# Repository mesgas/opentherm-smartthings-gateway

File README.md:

# OpenTherm ⇄ SmartThings gateway

A DIY **OpenTherm** gateway based on the ESP32-C3. It sits between your room thermostat and your boiler,
relays everything transparently, and lets you read and control the boiler from **SmartThings** through a
native **Edge driver** (no Matter, no Home Assistant).

```
thermostat ── T1/T2 [Slave shield]  ESP32-C3  [Master shield] B1/B2 ── boiler
                                       │ Wi-Fi, HTTP/JSON
                        SmartThings hub (Edge driver)  ──  SmartThings app
```

**Background:** I (the author) switched to Home Assistant two years ago and I am very happy with it. This project
was built for my father's boiler, in a household that still runs SmartThings. It is shared in the hope that it is
useful to other SmartThings users with an OpenTherm boiler. The HTTP/JSON API below can also be used from any
other home automation system.

---

## ⚠️ Important warnings

- **Experimental project, provided "as is", with no warranty of any kind** (see [LICENSE](LICENSE)).
- It involves **a gas appliance**. The gateway is wired **in series** between thermostat and boiler: if the
  ESP loses power or hangs, the thermostat can no longer talk to the boiler. Decide for yourself what
  happens in your installation in that case.
- The gateway can **switch heating off**, **cap the flow temperature**, and in "App command" mode it
  **replaces the thermostat**. It is not a safety device.
- Wiring on the boiler terminals must be done **with the power off** and, if you are not experienced,
  **by a qualified technician**. Never work on gas or 230 V parts.
- This project is not a product of any boiler manufacturer, DIYLess, Samsung or SmartThings.

---

## What it does

- **Relays transparently** every OpenTherm message between thermostat and boiler (it keeps working
  when Wi-Fi or SmartThings are unavailable).
- **Reads all the data that passes through** and asks the boiler for more in the thermostat's pauses:
  flow, return and hot water temperature, modulation, flame, faults, etc. (depending on what your boiler
  supports).
- **Controls from SmartThings:**
  - heating on/off (clears the "CH enable" bit in the status message);
  - domestic hot water on/off and setpoint;
  - flow temperature cap;
  - **App command**: the gateway regulates the room temperature towards a target set from SmartThings,
    using the temperature measured by the original thermostat;
  - **Auto flow**: the thermostat decides when to heat, the gateway computes the lowest possible flow
    temperature (useful with condensing boilers);
  - optional NTC outdoor probe: outdoor temperature, also provided to the thermostat.
- A local **HTTP/JSON API** for diagnostics and integration.

## Hardware

| Part | Notes |
|---|---|
| LOLIN (WEMOS) **C3 mini** | ESP32-C3, D1 mini form factor |
| **DIYLess Master OpenTherm shield** | boiler side (B1/B2) |
| **DIYLess Slave OpenTherm shield** | thermostat side (T1/T2) |
| Expansion shield (optional) | to mount the three boards side by side |
| 10 kΩ NTC probe (optional) | for the outdoor temperature, with a 10 kΩ resistor and a 100 nF capacitor |

Pins used (D1 mini position → C3 mini GPIO):

| Function | Position | GPIO |
|---|---|---|
| Master, OT input | D2 | 8 |
| Master, OT output | D1 | 10 |
| Slave, OT input | D6 | 0 |
| Slave, OT output | D7 | 4 |
| Outdoor probe (optional) | A0 | 3 |

They can be changed in [`src/config.h`](src/config.h). GPIO8 is a strapping pin of the ESP32-C3: if flashing
fails with the master shield mounted, remove the shield or hold BOOT.

**Outdoor probe (optional):** `3V3 ── R 10 kΩ ──┬── NTC ── GND`, with 100 nF between the node and GND and
the node connected to GPIO3. Enable it only after wiring it: `POST /api/settings {"outdoorEnabled":true}`.

## Firmware

1. Copy `src/secrets.example.h` to `src/secrets.h` and fill in your Wi-Fi (2.4 GHz). This file must never be
   committed (it is already in `.gitignore`).
2. `pio run -t upload` over USB the first time; later `pio run -e ota -t upload` for over-the-air updates
   (set `upload_port` in `platformio.ini`).
3. The serial monitor (115200) shows the IP, the relayed messages and the IDs requested by the thermostat.
4. Give the ESP a **fixed IP** in your router.
5. Optional: the ESP is reachable as `http://otgw.local/`. To change the name, add `#define HOSTNAME "my-boiler"` to `src/secrets.h`
   (and use it as `upload_port` in `platformio.ini`). Some phones cannot resolve `.local` names: use the IP address, or add a
   static DNS entry in your router.

Every boiler supports different OpenTherm IDs: use `GET /api/probe?id=N` to test yours and adapt
`POLL_IDS` in `config.h`.

## SmartThings driver (Edge)

**Quick install (driver only):** open this invitation link with the account that owns your hub, enroll the hub and
install the driver "OpenTherm Gateway" from the channel:

<https://bestow-regional.api.smartthings.com/invite/a5z2RPnwDj1n>

The custom capabilities live in the author's SmartThings namespace and should be usable from any account,
but this has only been tested on the author's account. Feedback is welcome (open an issue).

To build and publish your own copy (recommended if you want to modify anything), follow the steps below.

You need the [SmartThings CLI](https://github.com/SmartThingsCommunity/smartthings-cli) (on the first command
a browser opens for sign-in) and a hub that supports Edge drivers.

1. **Custom capabilities** (`capabilities/` folder): modulation, maximum flow temperature, hot water setpoint,
   boiler status. For each one:
   ```
   smartthings capabilities:create -i capabilities/<name>.json
   smartthings capabilities:presentation:create <namespace>.<name> --capability-version 1 -i capabilities/presentations/<name>.json
   smartthings capabilities:translations:upsert <namespace>.<name> --capability-version 1 -i capabilities/translations/<name>.it.json
   ```
2. In `driver/profiles/opentherm-gateway.yml` and in `driver/src/init.lua` replace the namespace
   `bookmusic32648` with **your own** namespace (the one assigned by your first `capabilities:create`).
3. Create a private channel, publish the driver and install it on your hub:
   ```
   smartthings edge:channels:create          (type DRIVER)
   smartthings edge:channels:enroll <hub-id> --channel <channel-id>
   smartthings edge:drivers:package driver --channel <channel-id> --hub <hub-id>
   ```
4. In the SmartThings app: add device → scan nearby → "OpenTherm Gateway", then in the device settings enter
   the **IP address of the ESP**.

If you change the **structure** of the profile (components or capabilities moved), delete the device in the
app and add it again; otherwise the app may show connection errors.

> **Note on languages:** the user-facing labels of the SmartThings device (component names in the profile
> and the capability presentations) are in Italian, because that is the language of the original household.
> Everything else (code, comments, logs, API, documentation) is in English. To localize the UI, edit the
> `label` fields in `driver/profiles/opentherm-gateway.yml` and the labels in `capabilities/presentations/`
> and `capabilities/translations/`.

### Device in SmartThings

Component ids in the profile are Italian technical identifiers (`main` = house, `comandoapp` = app command,
`riscaldamento` = heating, `mandataauto` = auto flow, `sanitaria` = hot water, `caldaia` = boiler,
`ritorno` = return, `esterna` = outdoor).

| Component | Content |
|---|---|
| Casa (House) | room temperature (from the original thermostat), Off/Heat mode, target, state |
| Comando da app (App command) | on = the app regulates, off = the wall thermostat decides |
| Riscaldamento (Heating) | switch, maximum flow temperature |
| Mandata auto (Auto flow) | switch |
| Acqua calda (Hot water) | switch, setpoint, temperature |
| Caldaia (Boiler) | flow temperature, modulation, status (flame, heating, hot water, thermostat, fault) |
| Ritorno, Esterna (Return, Outdoor) | temperature |

## Statistics page

Open `http://otgw.local/` (or the IP of the ESP) in a browser on your local network. Two views, switched with the
buttons at the top:

- **24 h:** one point every 5 minutes (stored per minute).
- **30 d:** one point every 3 hours (stored every 30 minutes).

Both show: flame-on time, heating and hot water time, burner starts, average modulation while the flame is on, the
share of burner time spent condensing (return below ~55 °C), and charts of temperatures (house, outdoor, flow,
return, requested flow), modulation/flame and heating/hot water duty. The page is Italian or English depending on
the browser language.

**Memory and persistence:** the last 24 hours are kept in RAM (about 26 KB, one bucket per minute) and are **cleared
when the ESP restarts**. The last 30 days (about 35 KB, one bucket per 30 minutes) are also kept in RAM but are
saved to flash (LittleFS) every hour and right before an OTA update, so they survive restarts, losing at most the
last hour. Lifetime burner hours and starts are saved to NVS every 30 minutes. Heavy requests (`/api/stats`,
`/api/history`) are limited to one every 2 seconds, because on a single core a flood of Wi-Fi traffic can disturb
the OpenTherm timing. The statistics are estimates built from the data the boiler reports.

## API

- `GET /api/state` — full state as JSON (`null` = value not available)
- `POST /api/settings` — JSON with one or more of: `chEnable`, `dhwEnable`, `chMax`, `dhwSetpoint`,
  `roomControl`, `roomTarget`, `flowAuto`, `outdoorEnabled`
- `GET /api/ids` — OpenTherm IDs requested by the thermostat and rejected by the boiler
- `GET /api/probe?id=N` — test read of one ID (read-only)
- `GET /` — statistics page
- `GET /api/stats[?range=30d]` — summary of the last 24 hours (default) or 30 days
- `GET /api/history[?range=30d][&step=N]` — history in points of N minutes (24 h, N ≥ 5) or N half-hours (30 d, N from 1 to 48)

If `API_TOKEN` in `secrets.h` is not empty, POST requests need the `X-Token` header. There is no encryption:
use it only on a trusted local network.

## Regulation (to be tuned)

The room temperature regulator (hysteresis + PI) and "Auto flow" use the `CTRL_*` parameters in
[`src/config.h`](src/config.h). The starting values are conservative but **theoretical**: they must be tuned by
watching how your house behaves. If your boiler does not provide the outdoor temperature, the flow ceiling is
fixed; with the outdoor probe it follows a heating curve.

## Known limitations

- The gateway has only been tested on a single installation.
- The API is not encrypted.
- With the gateway in series, an ESP failure interrupts the thermostat–boiler dialogue.
- The custom capabilities belong to a namespace: use your own if you want to modify them.

## Credits and license

- [OpenTherm Library](https://github.com/ihormelnyk/opentherm_library) by Ihor Melnyk (MIT).
- OpenTherm shields by [DIYLess](https://diyless.com).
- [ArduinoJson](https://arduinojson.org) by Benoit Blanchon (MIT).
- License of this project: **MIT** (see [LICENSE](LICENSE)).

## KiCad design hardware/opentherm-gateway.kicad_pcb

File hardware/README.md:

# Gateway PCB

A single compact board for the OpenTherm gateway: it replaces the LOLIN C3 mini + the two DIYLess
master/slave shields. It sits between the boiler and the original thermostat and runs the same
firmware as the breadboard version (`src/`, environment `gateway_pcb`).

> **Status: designed, DRC/ERC clean, not yet fabricated.** The OpenTherm front end is taken from an
> existing, working open design (see *Origin*), but the changes listed below are untested until the
> first board is built. Follow the bring-up sequence before connecting the boiler.

| | |
|---|---|
| Size | 56 x 42 mm, 4 layers (F / GND / GND+routing / B), parts on both sides |
| MCU | ESP32-C3-WROOM-02-N4 (Wi-Fi 2.4 GHz, antenna toward the top edge, nothing under it) |
| Power | USB-C (also native USB for flashing) **or** 5 V screw terminal J5; the two are OR-ed with Schottky diodes |
| Bus | J1 `BOILER` and J2 `THERM` (OpenTherm, polarity-free), 28 V TVS on both |
| Extra | J6 outdoor NTC 10 k (to 3V3 through a 10 k 0.1 % resistor), RESET / BOOT buttons, 3 status LEDs + 1 user LED |
| Mounting | 2 x M3 holes on a diagonal, 3.2 mm |

## Files

| Path | What |
|---|---|
| `opentherm-gateway.kicad_sch` / `.kicad_pcb` / `.kicad_pro` | KiCad 10 project |
| `production/opentherm-gateway-gerber.zip` | Gerbers + drill, ready for a PCB house |
| `production/bom.csv` | Bill of materials with LCSC part numbers (`bom-lcsc.csv` for the LCSC BOM tool, `bom-jlcpcb.csv` for JLCPCB assembly: one row per part number) |
| `production/positions.csv` | Pick-and-place, both sides (for reference; assembly is by hand) |
| `gen/` | Python generators: `design.py` is the single source of truth (parts + netlist), `gen_sch.py`, `build_pcb.py`, `route.py` (Freerouting), `export.py` |

The schematic is generated from the same netlist as the board (each pin carries a net label), so the
two cannot disagree. To change the design edit `gen/design.py` / `gen/placement.py` and re-run the
scripts (KiCad 10 python, Java for Freerouting).

## Origin and changes

The OpenTherm interface (opto-isolated master + slave, +24 V boost, current-sense circuits) is
derived from the *Arduino OpenTherm Shield* by MPro (Michal Protasowicki, CERN-OHL-P-2.0,
<https://github.com/michpro/Arduino_OpenTherm_shield>), which is itself based on the OpenTherm
Gateway of Schelte Bron (<https://otgw.tclcode.com>). This board keeps that circuit and changes:

* the Arduino header is replaced by the ESP32-C3 module, a 3.3 V LDO (AP2112K) and USB-C;
* logic runs at 3.3 V, the boost converter is fed from 5 V;
* the LED of the optocoupler towards the boiler (U2) is driven low-side from the GPIO, so that the
  line polarity matches the OpenTherm library used by the firmware (idle = HIGH output);
* added: TVS on both bus terminals, outdoor NTC input, user LED, UART test pads (TP8/TP9).

Released under the same license, CERN-OHL-P-2.0.

## GPIO map (ESP32-C3)

| GPIO | Net | Function |
|---|---|---|
| IO4 | SLAVE_IN | from the boiler (opto U3) = `PIN_M_IN` in firmware |
| IO5 | SLAVE_OUT | towards the boiler (opto U2) = `PIN_M_OUT` |
| IO6 | MASTER_IN | from the thermostat = `PIN_S_IN` |
| IO7 | MASTER_OUT | towards the thermostat = `PIN_S_OUT` |
| IO3 | NTC_ADC | outdoor probe (J6) |
| IO10 | LED_USER | user LED (not used by the firmware yet) |
| IO18 / IO19 | USB D- / D+ | native USB (USB-C) |
| IO9 | BOOT | boot button (hold while pressing RESET to enter the ROM bootloader) |
| IO2 / IO8 | | strapping pins, pulled up |
| IO20 / IO21 | RXD / TXD | UART0 test pads TP9 / TP8 |

## Bring-up (do this in order, boiler disconnected)

1. Visual check, then measure resistance between `GND` and `+5V`, `+3V3`, `+24V` (no shorts).
2. Power from USB only. `+5V` ~ 4.7 V (one diode drop), `+3V3` = 3.3 V (TP1), `+24V` ~ 24 V (TP3).
   If `+24V` is wrong check R1 (240 k) / R2 (13 k): Vout = 1.25 V x (1 + R1/R2).
3. Flash `gateway_pcb` over USB (`pio run -e gateway_pcb -t upload`; if the port does not appear,
   hold BOOT and tap RESET).
4. With nothing on J1/J2 the PWR LED is on and RxB/RxT are off. Connect only the thermostat to J2:
   measure `T+` (TP4) and check that the RxT LED blinks on each thermostat message.
5. Connect the boiler to J1 last. The gateway must relay: check `/api/status` and the LEDs.
6. If the boiler status stays INVALID while the thermostat talks, the polarity of the line towards
   the boiler is the first thing to check (see the note on U2 above).

## Ordering notes

* 4 layers, 1.6 mm, FR-4, HASL is fine. Min track/space used: 0.15 / 0.2 mm, min drill 0.3 mm.
* Hand assembly: all passives are 0805, the ESP32 module has its pads on the underside (hot air and
  flux). Parts are on both sides; do the side with the module first.
* The BOM has an LCSC code for every part (checked against the JLCPCB parts library, all in stock when
  checked). Equivalent parts can be substituted; the screw terminals (KF350-3.5-2P) and the inductor
  should be compared with their datasheets against the footprints before ordering.
* RxB is a green LED (R17 = 330 ohm), PWR red, RxT yellow, USER red.

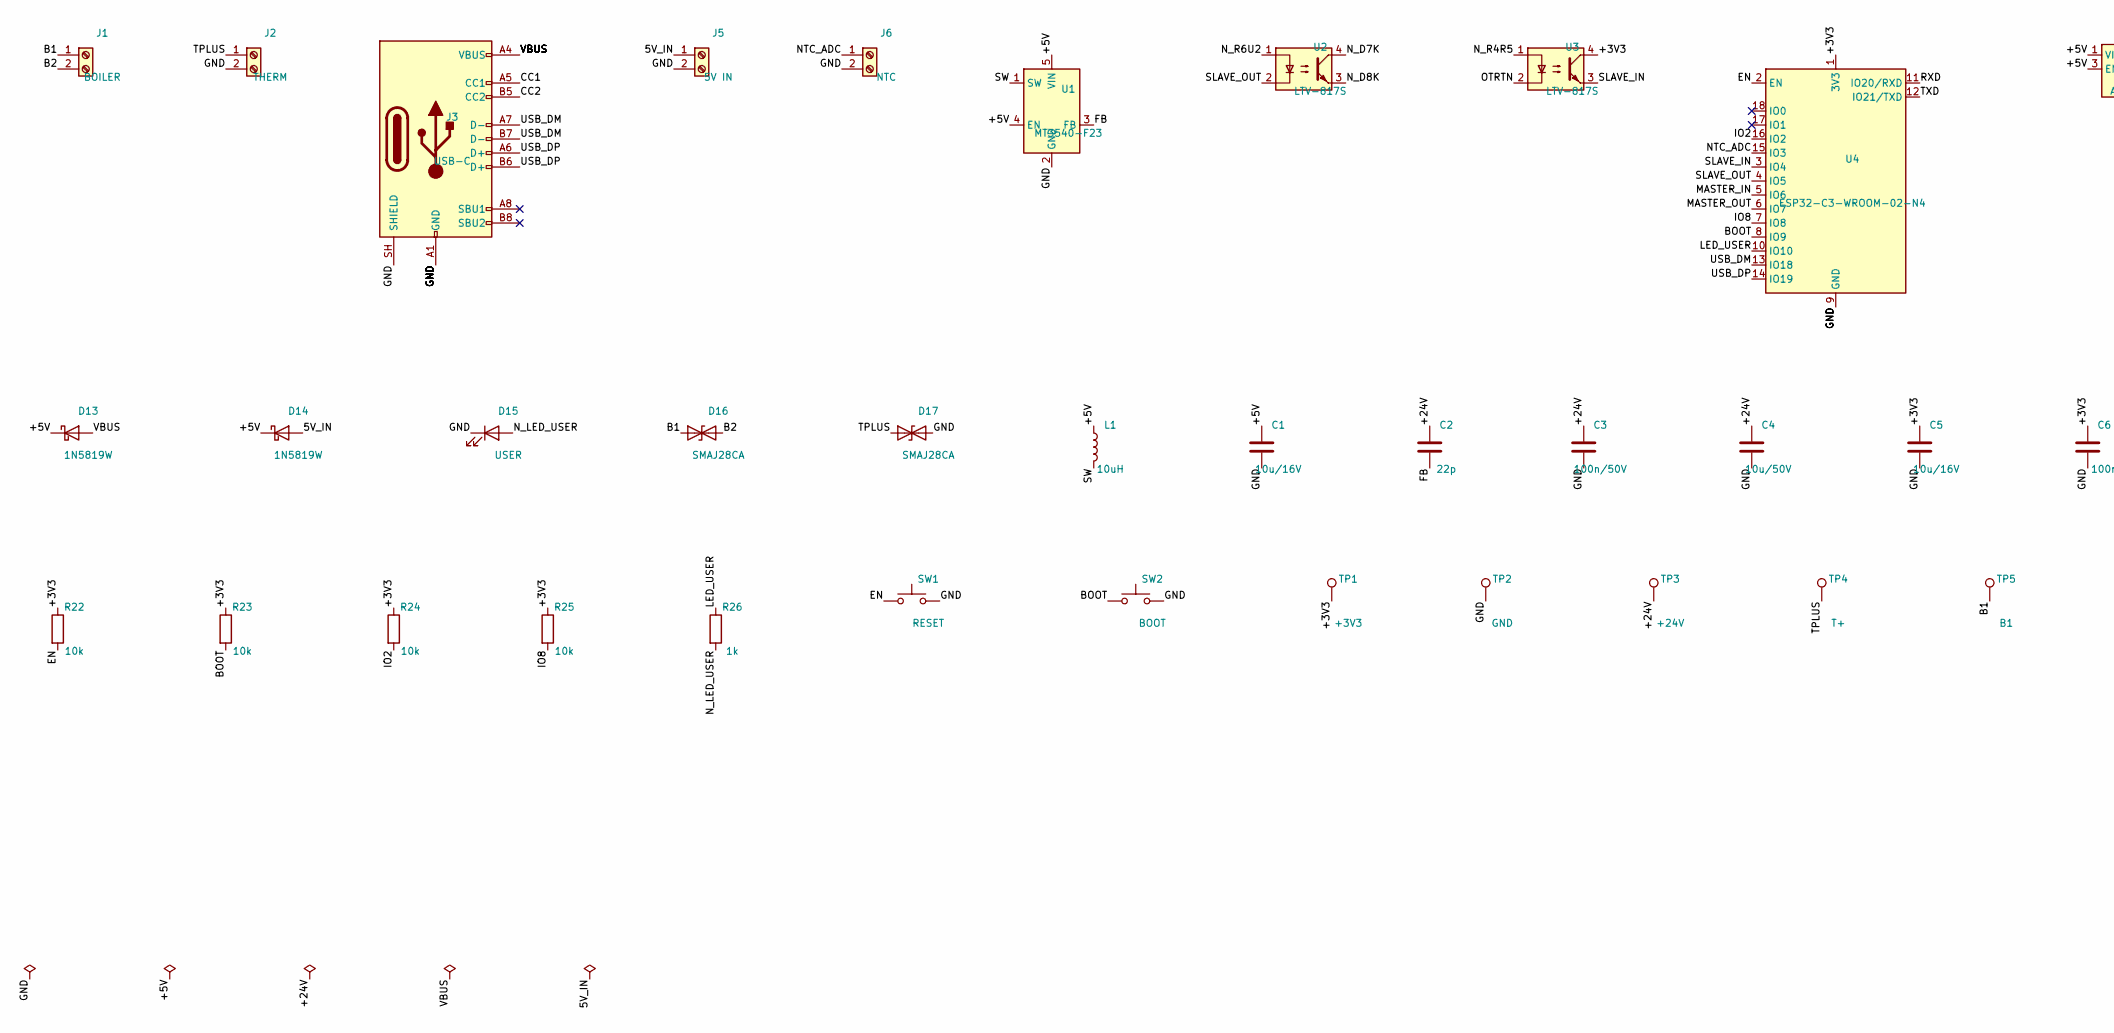
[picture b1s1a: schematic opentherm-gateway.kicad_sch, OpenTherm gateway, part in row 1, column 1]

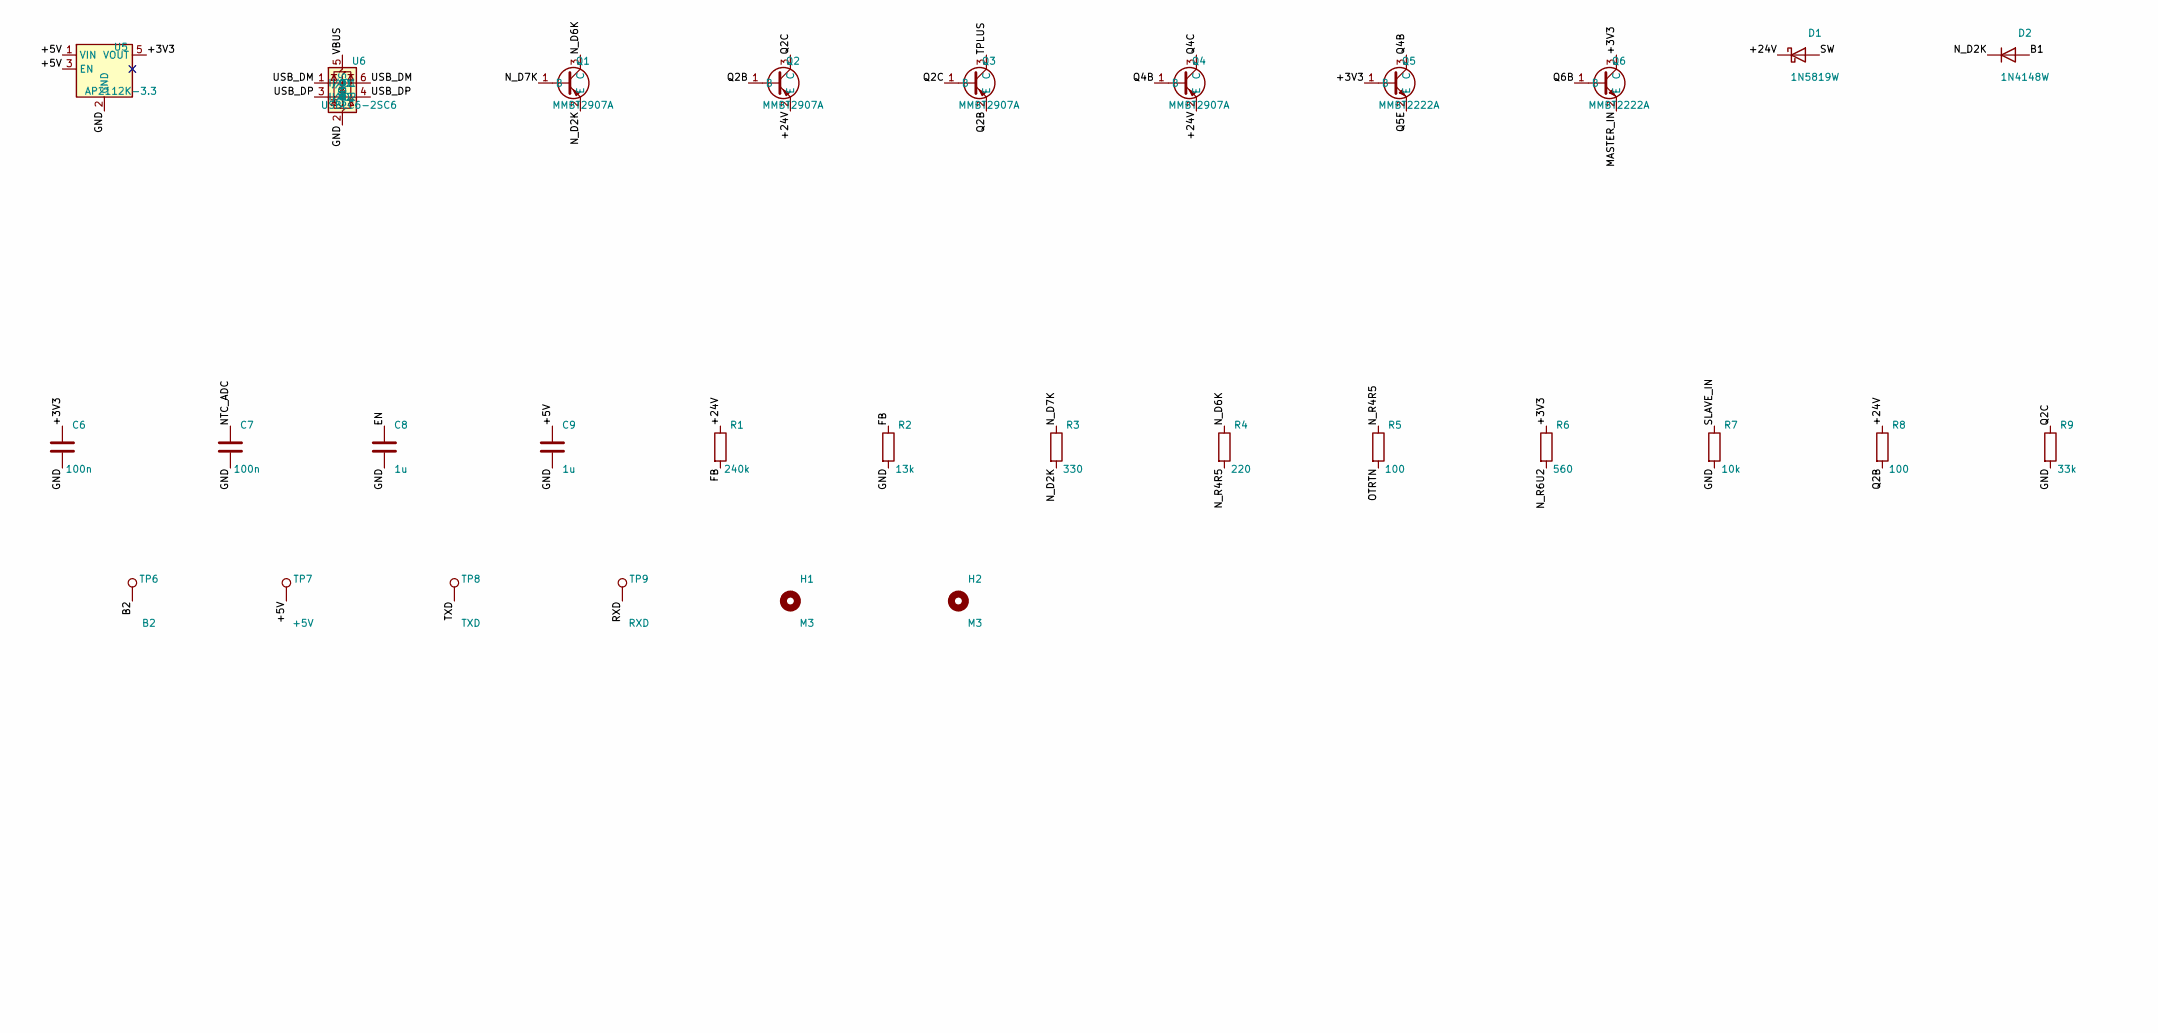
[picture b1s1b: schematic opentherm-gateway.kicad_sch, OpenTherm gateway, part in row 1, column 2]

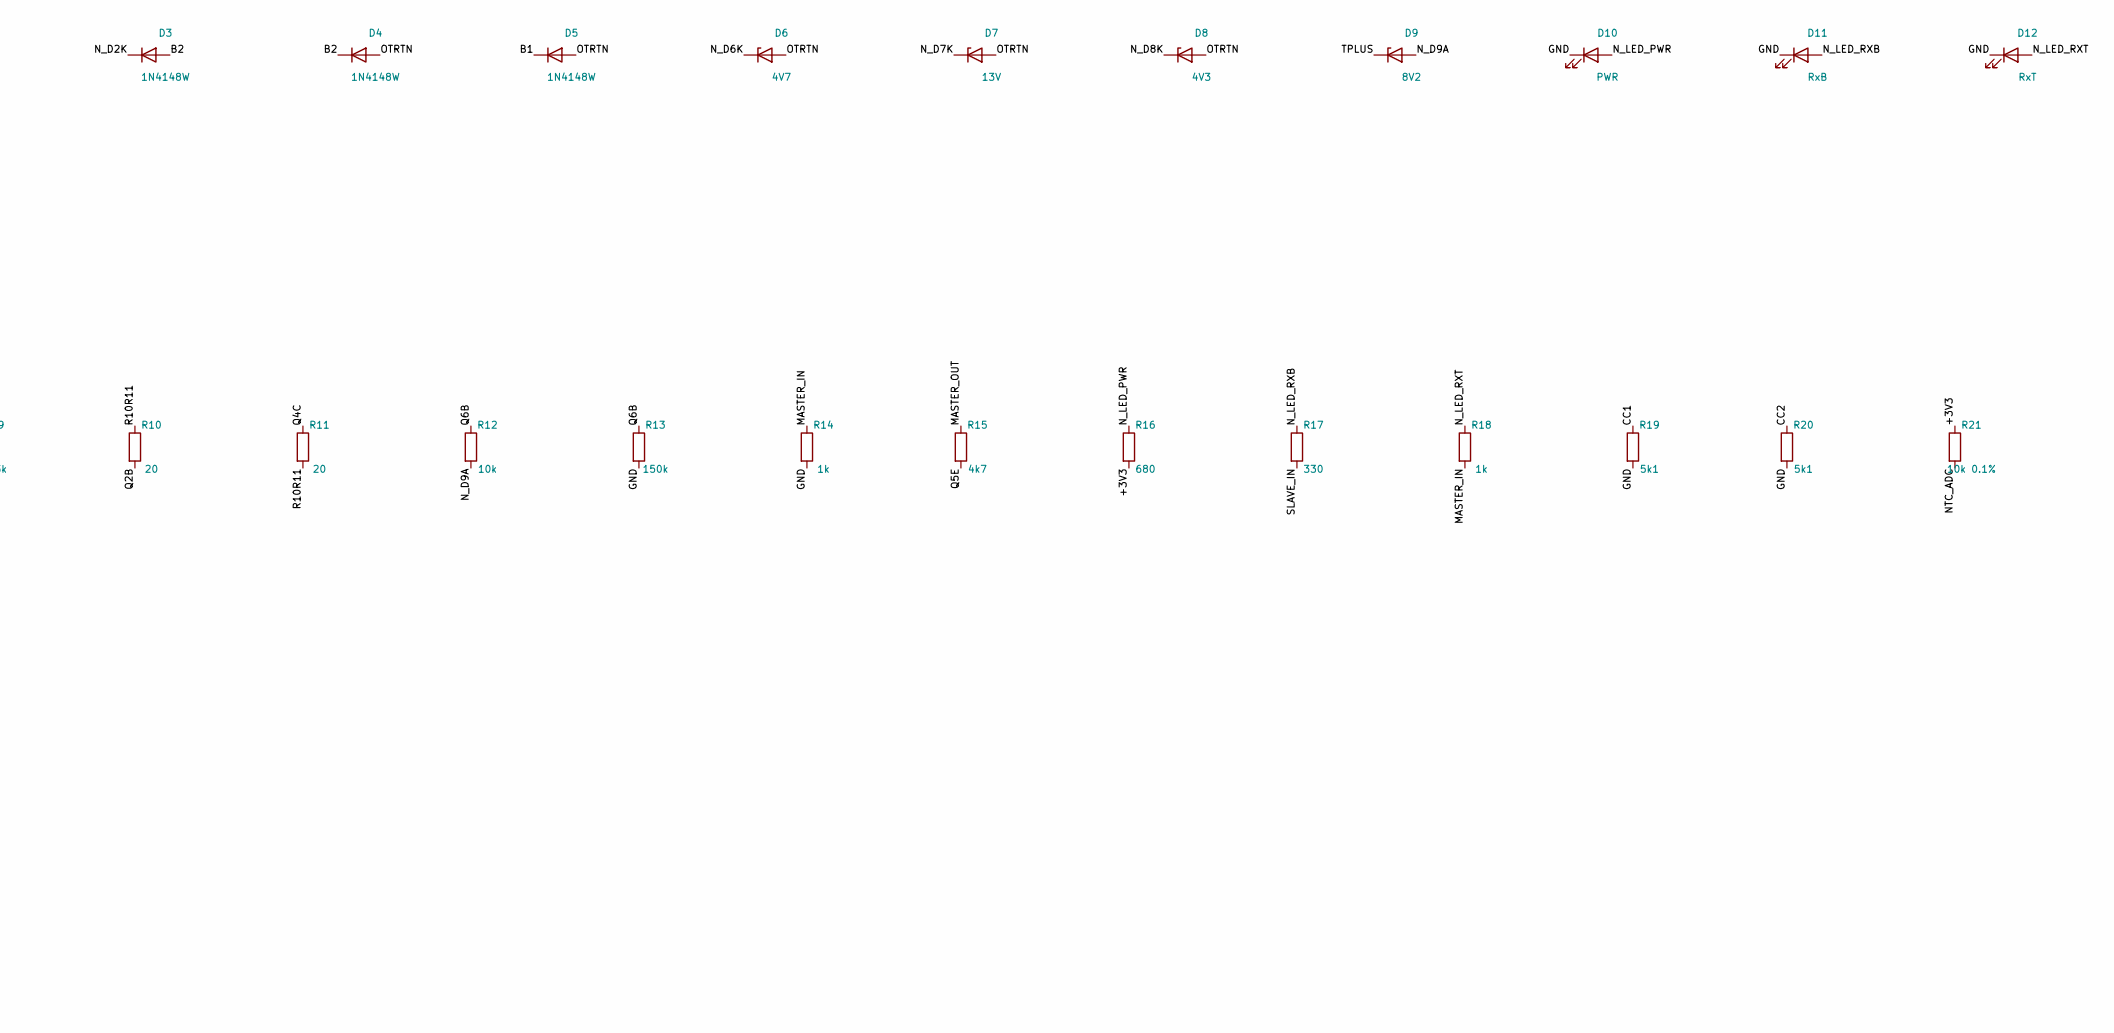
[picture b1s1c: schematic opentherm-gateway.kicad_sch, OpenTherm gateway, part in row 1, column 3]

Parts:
C1, C5: 10u/16V; C_0805_2012Metric; LCSC C1713
C2: 22p; C_0805_2012Metric; LCSC C1804
C3: 100n/50V; C_0805_2012Metric; LCSC C49678
C4: 10u/50V; C_0805_2012Metric; LCSC C440198
C6, C7: 100n; C_0805_2012Metric; LCSC C49678
C8, C9: 1u; C_0805_2012Metric; LCSC C28323
D1, D13, D14: 1N5819W; D_SOD-123; LCSC C8598
D2, D3, D4, D5: 1N4148W; D_SOD-123; LCSC C7420318
D6: 4V7; D_SOD-123; LCSC C19077400
D7: 13V; D_SOD-123; LCSC C22399883
D8: 4V3; D_SOD-123; LCSC C19077399
D9: 8V2; D_SOD-123; LCSC C22399882
D10: PWR; LED_0805_2012Metric; LCSC C84256
D11: RxB; LED_0805_2012Metric; LCSC C2297
D12: RxT; LED_0805_2012Metric; LCSC C2296
D15: USER; LED_0805_2012Metric; LCSC C84256
D16, D17: SMAJ28CA; D_SMA; LCSC C113964
H1, H2: M3; MountingHole_3.2mm_M3
J1: BOILER; TerminalBlock_4Ucon_1x02_P3.50mm_Horizontal; LCSC C474892
J2: THERM; TerminalBlock_4Ucon_1x02_P3.50mm_Horizontal; LCSC C474892
J3: USB-C; USB_C_Receptacle_HRO_TYPE-C-31-M-12; LCSC C165948
J5: 5V IN; TerminalBlock_4Ucon_1x02_P3.50mm_Horizontal; LCSC C474892
J6: NTC; TerminalBlock_4Ucon_1x02_P3.50mm_Horizontal; LCSC C474892
L1: 10uH; L_Bourns-SRN4018; LCSC C177242
Q1, Q2, Q3, Q4: MMBT2907A; SOT-23; LCSC C7420352
Q5, Q6: MMBT2222A; SOT-23; LCSC C8512
R1: 240k; R_0805_2012Metric; LCSC C25824
R2: 13k; R_0805_2012Metric; LCSC C17455
R3, R17: 330; R_0805_2012Metric; LCSC C17630
R4: 220; R_0805_2012Metric; LCSC C17557
R5, R8: 100; R_0805_2012Metric; LCSC C17408
R6: 560; R_0805_2012Metric; LCSC C28636
R7, R12, R22, R23, R24, R25: 10k; R_0805_2012Metric; LCSC C17414
R9: 33k; R_0805_2012Metric; LCSC C17633
R10, R11: 20; R_0805_2012Metric; LCSC C17544
R13: 150k; R_0805_2012Metric; LCSC C17470
R14, R18, R26: 1k; R_0805_2012Metric; LCSC C17513
R15: 4k7; R_0805_2012Metric; LCSC C17673
R16: 680; R_0805_2012Metric; LCSC C17798
R19, R20: 5k1; R_0805_2012Metric; LCSC C27834
R21: 10k 0.1%; R_0805_2012Metric; LCSC C110775
SW1: RESET; SW_Push_1P1T_NO_CK_KMR2; LCSC C72443
SW2: BOOT; SW_Push_1P1T_NO_CK_KMR2; LCSC C72443
TP1: +3V3; TestPoint_Pad_D1.5mm
TP2: GND; TestPoint_Pad_D1.5mm
TP3: +24V; TestPoint_Pad_D1.5mm
TP4: T+; TestPoint_Pad_D1.5mm
TP5: B1; TestPoint_Pad_D1.5mm
TP6: B2; TestPoint_Pad_D1.5mm
TP7: +5V; TestPoint_Pad_D1.5mm
TP8: TXD; TestPoint_Pad_D1.5mm
TP9: RXD; TestPoint_Pad_D1.5mm
U1: MT3540-F23; SOT-23-5; LCSC C181783
U2, U3: LTV-817S; SMDIP-4_W9.53mm; LCSC C109227
U4: ESP32-C3-WROOM-02-N4; ESP32-C3-WROOM-02; LCSC C2934560
U5: AP2112K-3.3; SOT-23-5; LCSC C51118
U6: USBLC6-2SC6; SOT-23-6; LCSC C7519

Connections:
5V_IN: D14.2 (A), J5.1
+3V3: C5.1, C6.1, Q5.1 (B), Q6.3 (C), R6.1, R16.2, R21.1, R22.1, R23.1, R24.1, R25.1, TP1.1, U3.4, U4.1 (3V3), U5.5 (VOUT)
+5V: C1.1, C9.1, D13.1 (K), D14.1 (K), L1.1, TP7.1, U1.4 (EN), U1.5 (VIN), U5.1 (VIN), U5.3 (EN)
+24V: C2.1, C3.1, C4.1, D1.1 (K), Q2.2 (E), Q4.2 (E), R1.1, R8.1, TP3.1
B1: D2.2 (A), D5.1 (K), D16.1 (A1), J1.1, TP5.1
B2: D3.2 (A), D4.1 (K), D16.2 (A2), J1.2, TP6.1
BOOT: R23.2, SW2.1, U4.8 (IO9)
CC1: J3.A5 (CC1), R19.1
CC2: J3.B5 (CC2), R20.1
EN: C8.1, R22.2, SW1.1, U4.2 (EN)
FB: C2.2, R1.2, R2.1, U1.3 (FB)
GND: C1.2, C3.2, C4.2, C5.2, C6.2, C7.2, C8.2, C9.2, D10.1 (K), D11.1 (K), D12.1 (K), D15.1 (K), D17.2 (A2), J2.2, J3.A1 (GND), J3.A12 (GND), J3.B1 (GND), J3.B12 (GND), J3.SH (SHIELD), J5.2, J6.2, R2.2, R7.2, R9.2, R13.2, R14.2, R19.2, R20.2, SW1.2, SW2.2, TP2.1, U1.2 (GND), U4.9 (GND), U4.19 (GND), U5.2 (GND), U6.2 (GND)
IO2: R24.2, U4.16 (IO2)
IO8: R25.2, U4.7 (IO8)
LED_USER: R26.1, U4.10 (IO10)
MASTER_IN: Q6.2 (E), R14.1, R18.2, U4.5 (IO6)
MASTER_OUT: R15.1, U4.6 (IO7)
NTC_ADC: C7.1, J6.1, R21.2, U4.15 (IO3)
N_D2K: D2.1 (K), D3.1 (K), Q1.2 (E), R3.2
N_D6K: D6.1 (K), Q1.3 (C), R4.1
N_D7K: D7.1 (K), Q1.1 (B), R3.1, U2.4
N_D8K: D8.1 (K), U2.3
N_D9A: D9.2 (A), R12.2
N_LED_PWR: D10.2 (A), R16.1
N_LED_RXB: D11.2 (A), R17.1
N_LED_RXT: D12.2 (A), R18.1
N_LED_USER: D15.2 (A), R26.2
N_R4R5: R4.2, R5.1, U3.1
N_R6U2: R6.2, U2.1
OTRTN: D4.2 (A), D5.2 (A), D6.2 (A), D7.2 (A), D8.2 (A), R5.2, U3.2
Q2B: Q2.1 (B), Q3.2 (E), R8.2, R10.2
Q2C: Q2.3 (C), Q3.1 (B), R9.1
Q4B: Q4.1 (B), Q5.3 (C)
Q4C: Q4.3 (C), R11.1
Q5E: Q5.2 (E), R15.2
Q6B: Q6.1 (B), R12.1, R13.1
R10R11: R10.1, R11.2
RXD: TP9.1, U4.11 (IO20/RXD)
SLAVE_IN: R7.1, R17.2, U3.3, U4.3 (IO4)
SLAVE_OUT: U2.2, U4.4 (IO5)
SW: D1.2 (A), L1.2, U1.1 (SW)
TPLUS: D9.1 (K), D17.1 (A1), J2.1, Q3.3 (C), TP4.1
TXD: TP8.1, U4.12 (IO21/TXD)
USB_DM: J3.A7 (D-), J3.B7 (D-), U4.13 (IO18), U6.1 (I/O1), U6.6 (I/O1)
USB_DP: J3.A6 (D+), J3.B6 (D+), U4.14 (IO19), U6.3 (I/O2), U6.4 (I/O2)
VBUS: D13.2 (A), J3.A4 (VBUS), J3.A9 (VBUS), J3.B4 (VBUS), J3.B9 (VBUS), U6.5 (VBUS)

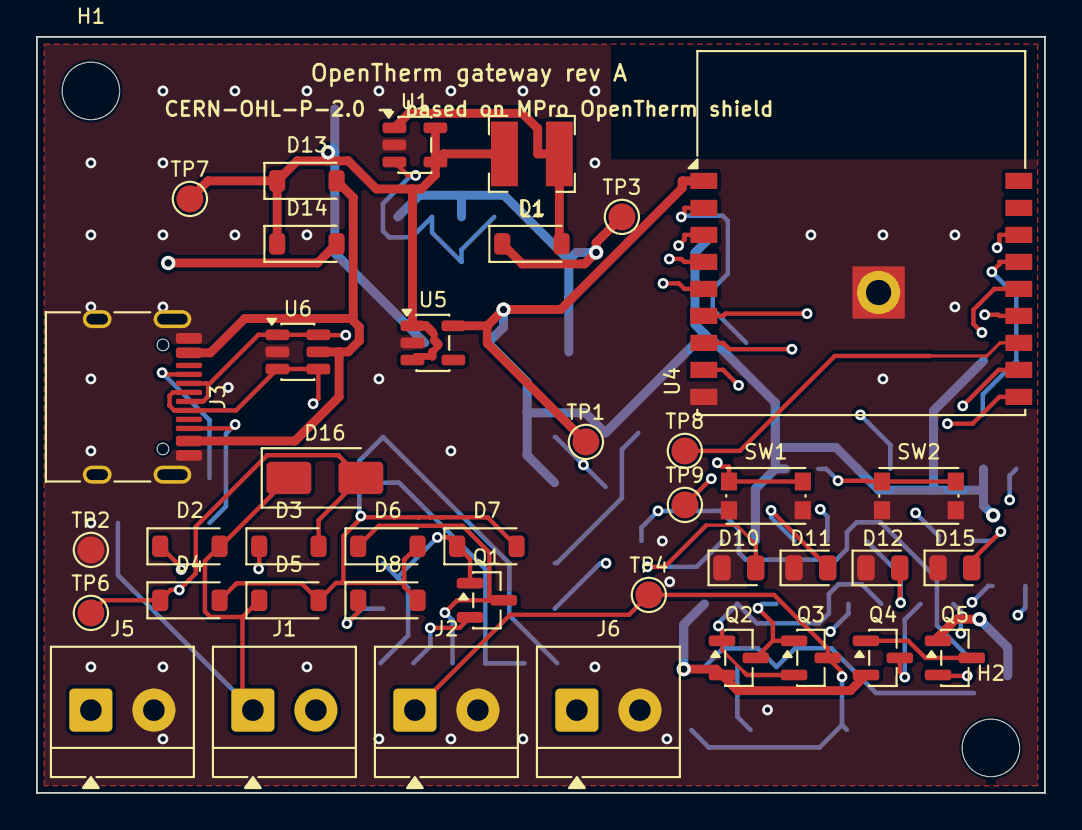
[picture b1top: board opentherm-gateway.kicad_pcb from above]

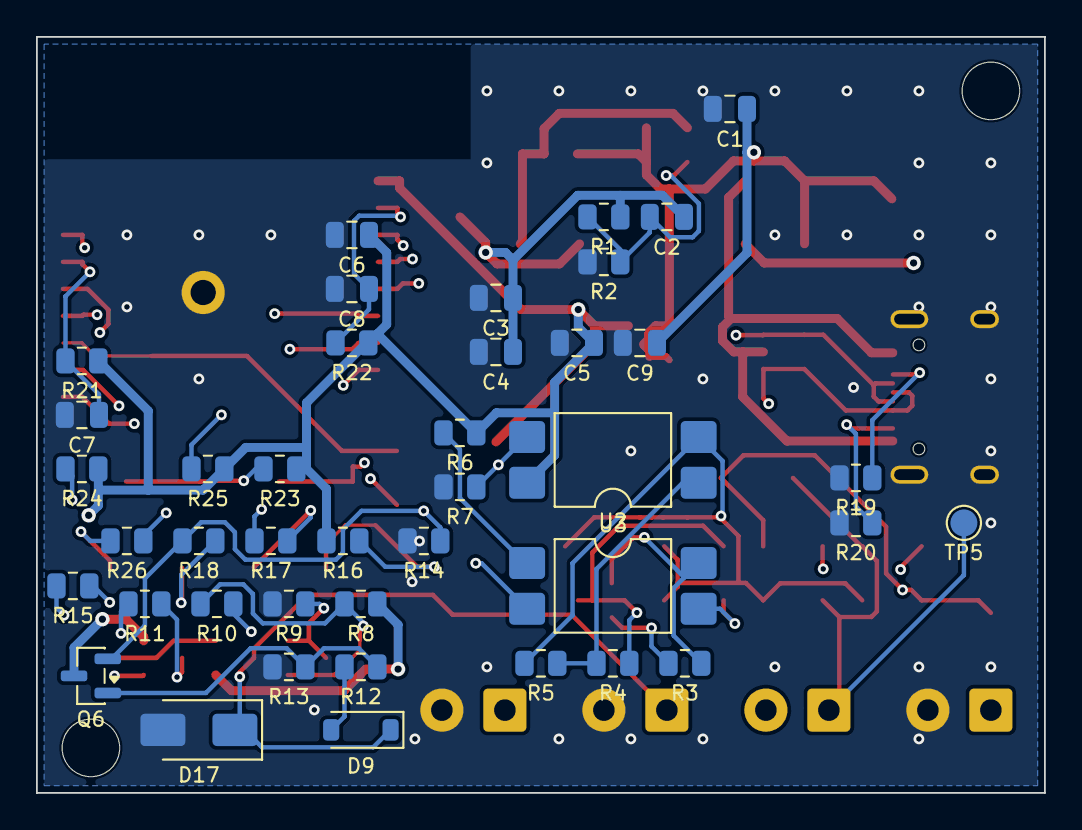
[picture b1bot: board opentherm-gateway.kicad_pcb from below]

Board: 4 copper layers, 56.0 x 42.0 mm, 83 parts (41 on the bottom side), 46 nets.

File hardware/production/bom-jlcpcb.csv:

Comment,Designator,Footprint,LCSC Part #
10u/16V,C1,C_0805_2012Metric,C1713
22p,C2,C_0805_2012Metric,C1804
100n/50V,C3,C_0805_2012Metric,C49678
10u/50V,C4,C_0805_2012Metric,C440198
10u/16V,C5,C_0805_2012Metric,C1713
100n,C6,C_0805_2012Metric,C49678
100n,C7,C_0805_2012Metric,C49678
1u,C8,C_0805_2012Metric,C28323
1u,C9,C_0805_2012Metric,C28323
1N5819W,D1,D_SOD-123,C8598
1N4148W,"D2,D3,D4,D5",D_SOD-123,C7420318
4V7,D6,D_SOD-123,C19077400
13V,D7,D_SOD-123,C22399883
4V3,D8,D_SOD-123,C19077399
8V2,D9,D_SOD-123,C22399882
PWR,D10,LED_0805_2012Metric,C84256
RxB,D11,LED_0805_2012Metric,C2297
RxT,D12,LED_0805_2012Metric,C2296
1N5819W,D13,D_SOD-123,C8598
1N5819W,D14,D_SOD-123,C8598
USER,D15,LED_0805_2012Metric,C84256
SMAJ28CA,D16,D_SMA,C113964
SMAJ28CA,D17,D_SMA,C113964
BOILER,J1,TerminalBlock_4Ucon_1x02_P3.50mm_Horizontal,C474892
THERM,J2,TerminalBlock_4Ucon_1x02_P3.50mm_Horizontal,C474892
USB-C,J3,USB_C_Receptacle_HRO_TYPE-C-31-M-12,C165948
5V IN,J5,TerminalBlock_4Ucon_1x02_P3.50mm_Horizontal,C474892
NTC,J6,TerminalBlock_4Ucon_1x02_P3.50mm_Horizontal,C474892
10uH,L1,L_Bourns-SRN4018,C177242
MMBT2907A,"Q1,Q2,Q3,Q4",SOT-23,C7420352
MMBT2222A,"Q5,Q6",SOT-23,C8512
240k,R1,R_0805_2012Metric,C25824
13k,R2,R_0805_2012Metric,C17455
330,R3,R_0805_2012Metric,C17630
220,R4,R_0805_2012Metric,C17557
100,"R5,R8",R_0805_2012Metric,C17408
560,R6,R_0805_2012Metric,C28636
10k,"R7,R12",R_0805_2012Metric,C17414
33k,R9,R_0805_2012Metric,C17633
20,"R10,R11",R_0805_2012Metric,C17544
150k,R13,R_0805_2012Metric,C17470
1k,R14,R_0805_2012Metric,C17513
4k7,R15,R_0805_2012Metric,C17673
680,R16,R_0805_2012Metric,C17798
330,R17,R_0805_2012Metric,C17630
1k,R18,R_0805_2012Metric,C17513
5k1,R19,R_0805_2012Metric,C27834
5k1,R20,R_0805_2012Metric,C27834
10k 0.1%,R21,R_0805_2012Metric,C110775
10k,R22,R_0805_2012Metric,C17414
10k,R23,R_0805_2012Metric,C17414
10k,R24,R_0805_2012Metric,C17414
10k,R25,R_0805_2012Metric,C17414
1k,R26,R_0805_2012Metric,C17513
RESET,SW1,SW_Push_1P1T_NO_CK_KMR2,C72443
BOOT,SW2,SW_Push_1P1T_NO_CK_KMR2,C72443
MT3540-F23,U1,SOT-23-5,C181783
LTV-817S,U2,SMDIP-4_W9.53mm,C109227
LTV-817S,U3,SMDIP-4_W9.53mm,C109227
ESP32-C3-WROOM-02-N4,U4,ESP32-C3-WROOM-02,C2934560
AP2112K-3.3,U5,SOT-23-5,C51118
USBLC6-2SC6,U6,SOT-23-6,C7519

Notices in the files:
hardware/opentherm-gateway.kicad_pcb:
CERN-OHL-P-2.0 - based on MPro OpenTherm shield
hardware/opentherm-gateway.kicad_sch:
Derived from the MPro Arduino OpenTherm shield (CERN-OHL-P-2.0)
